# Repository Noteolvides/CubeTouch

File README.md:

## What is it?
A cube made up of 6 PCBs that when soldered together form a cube universe.
CubeTouch is designed to create a beautiful object from PCBs but giving it all the functionality of a HID device, being able to interact with the computer as if it were a keyboard or any other HID device. 

CubeTouch is made up of the **CH552** micontroller and 6 WS2812 LEDs that illuminate the planets thanks to the diffusion of the FR4 material. This device is already loaded with a firmware that when pressing one of the 5 planets will send a combination of keys to the computer. These can be modified on the 

# Documentation and more
CubeTouch has its own [webPage](https://cubetouch.noteolvid.es/) where you can find, how to [program the device](https://cubetouch.noteolvid.es/docs/firstSteps/programming/), [examples](https://cubetouch.noteolvid.es/docs/firstSteps/examples/) and much more😊!

## Examples
### Custom Firmware
Default firmware that comes preload with the package. Its main function is to use as an external keyboard with shortcuts to increase your productivity in your daily work in the computer.
Each face is mapped with a possible combination of 3 keys, and a color to show that the keys were sent.
These can be remapped via the [web interface](https://cubetouch.noteolvid.es/keyRemapping/) thanks to [web serial](https://web.dev/serial/).
### [Easy RGB](https://cubetouch.noteolvid.es/docs/firstSteps/examples/#easy-rgb)
A simple example that receives an RGB hex value and displays it. Send hex color to the Serial Monitor following this format (R,G,B): #0B4F02
### [Chasse Lights](https://cubetouch.noteolvid.es/docs/firstSteps/examples/#chasse-text)
Moving lights.
### [Easy Touch](https://cubetouch.noteolvid.es/docs/firstSteps/examples/#easy-touch)
A simple example that when a face is touch prints the face that has received input from.
### [CDC and Keyboard](https://cubetouch.noteolvid.es/docs/firstSteps/examples/#cdc-and-keyboard)
This example echoes the next character of data it receives via the serial monitor and sends as a key also the next character send.
### [Custom Bootloader](https://cubetouch.noteolvid.es/docs/firstSteps/examples/#custom-bootloader)
This example that shows how to jump to the bootloader address to make it reprogrammable. You can send the character B, or connect the pin 11 to GND.

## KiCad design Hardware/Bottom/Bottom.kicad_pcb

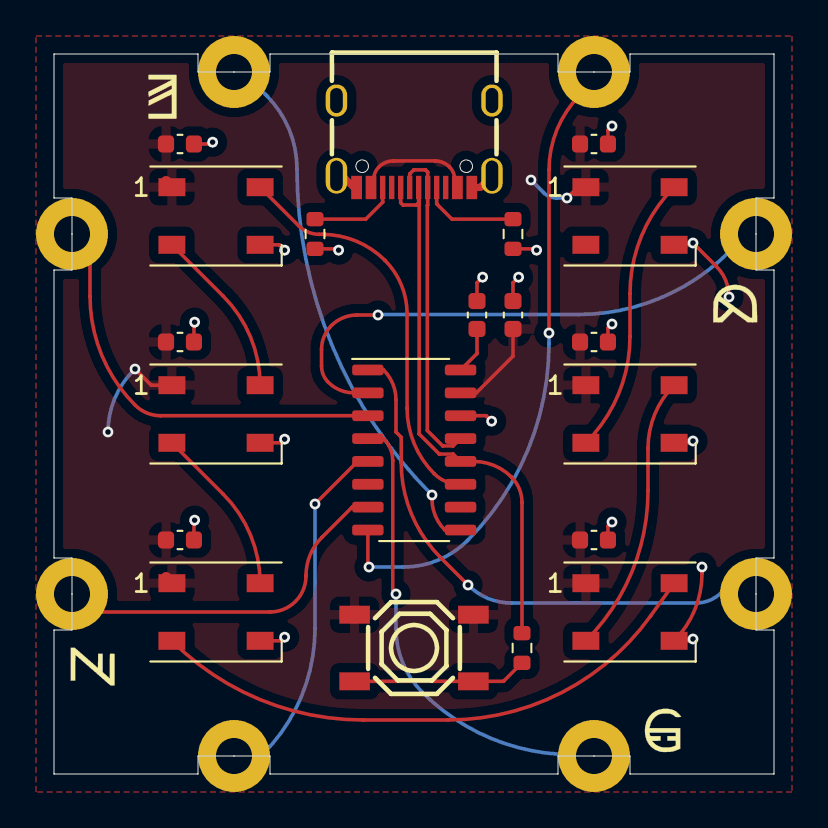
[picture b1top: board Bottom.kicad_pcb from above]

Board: 2 copper layers, 40.0 x 40.0 mm, 28 parts (0 on the bottom side), 22 nets.

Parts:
C1, C2, C3, C4, C5, C6, C7, C8: 0.1uf; C_0603_1608Metric
D1, D2, D3, D4, D5, D6: WS2812B; LED_WS2812B_PLCC4_5.0x5.0mm_P3.2mm
J1: USB_C_Receptacle_USB2.0; USB-C-SMD_KH-TYPE-C-16P
J2: Quamtum Front; Castelated
J3: Gargantua Top; Castelated
J4: Zebrum Left; Castelated
J5: Dune Right; Castelated
J6: Enkrusion Back; Castelated
J7: 3.2; Castelated
J8: 3.1; Castelated
J9: 3.0; Castelated
R1, R2: 5.1K; R_0603_1608Metric
R3: 10K; R_0603_1608Metric
SW1: Tactile Button; SW-SMD_4P-L5.1-W5.1-P3.70-LS6.5-TL-2
U1: CH552G; SO-16_3.9x9.9mm_P1.27mm

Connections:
+3V3: C2.1, U1.16 (V3.3)
DATA_LEDS: D1.4 (DIN), U1.11 (P3.4)
GND: C1.2, C2.2, C3.2, C4.2, C5.2, C6.2, C7.2, C8.2, D1.3 (VSS), D2.3 (VSS), D3.3 (VSS), D4.3 (VSS), D5.3 (VSS), D6.3 (VSS), J1.A1 (GND), J1.A12 (GND), J1.B1 (GND), J1.B12 (GND), J1.S1 (SHIELD), R1.2, R2.2, U1.14 (GND)
unnamed: D1.2 (DOUT), D2.4 (DIN)
unnamed: D2.2 (DOUT), D3.4 (DIN)
unnamed: D3.2 (DOUT), D4.4 (DIN)
unnamed: D4.2 (DOUT), D5.4 (DIN)
unnamed: D5.2 (DOUT), D6.4 (DIN)
unnamed: J1.A5 (CC1), R1.1
unnamed: J1.B5 (CC2), R2.1
unnamed: J2.1, U1.5 (P1.7)
unnamed: J3.1, U1.4 (P1.6)
unnamed: J4.1, U1.3 (P1.5)
unnamed: J5.1, U1.2 (P1.5)
unnamed: J6.1, U1.9 (P1.1)
unnamed: J7.1, U1.1 (P3.2)
unnamed: J8.1, U1.7 (P3.1)
unnamed: J9.1, U1.8 (P3.0)
unnamed: R3.2, SW1.1 (A), SW1.2 (B)
UD+: J1.A6 (D+), J1.B6 (D+), R3.1, U1.12 (P3.6)
UD-: J1.A7 (D-), J1.B7 (D-), U1.13 (P3.7)
VBUS: C1.1, C3.1, C4.1, C5.1, C6.1, C7.1, C8.1, D1.1 (VDD), D2.1 (VDD), D3.1 (VDD), D4.1 (VDD), D5.1 (VDD), D6.1 (VDD), J1.A4 (VBUS), J1.A9 (VBUS), J1.B4 (VBUS), J1.B9 (VBUS), SW1.3 (C), SW1.4 (D), U1.15 (VCC)

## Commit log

2022-01-11 init commit
2022-01-11 Init Docusaurus
2022-01-16 KeyRemapping page
2022-01-16 Added Navbar links
2022-02-06 Added docs pages
2022-02-19 Added build page
2022-02-19 Create CNAME
2022-02-19 Change baseurl
2022-02-19 Fix build
2022-02-19 Added website folder
2022-02-19 deploy: 8e7ee602b4856268e78e5021084b8bd6e064e6e0
2022-02-19 deploy: f38a8eda8bc669222fd8a9f3aa16f63e1f32a57d
2022-02-20 Added more documentation
2022-02-20 Changed github repo name
2022-02-20 deploy: 181a65fe0b3fea9ad272537e2484f867ba803c1b
2022-02-20 Deleted idea folder
2022-02-20 Deleted idea blog folder
2022-02-27 Added Examples
2022-02-27 deploy: 0cbf2b3b16d8daa06b9ea906c19a8e8f4b78ee8c
2022-02-27 Added Show code
2022-02-27 Bump prismjs from 1.26.0 to 1.27.0 in /website
    Bumps [prismjs](https://github.com/PrismJS/prism) from 1.26.0 to 1.27.0.
    - [Release notes](https://github.com/PrismJS/prism/releases)
    - [Changelog](https://github.com/PrismJS/prism/blob/master/CHANGELOG.md)
    - [Commits](https://github.com/PrismJS/prism/compare/v1.26.0...v1.27.0)
    ---
    updated-dependencies:
2022-02-27 Fix Static generation
2022-02-27 Fix package.json
2022-02-27 Fix showCode import
2022-02-27 Bump follow-redirects from 1.14.7 to 1.14.9 in /website
    Bumps [follow-redirects](https://github.com/follow-redirects/follow-redirects) from 1.14.7 to 1.14.9.
    - [Release notes](https://github.com/follow-redirects/follow-redirects/releases)
    - [Commits](https://github.com/follow-redirects/follow-redirects/compare/v1.14.7...v1.14.9)
    ---
    updated-dependencies:
    - dependency-name: follow-redirects
2022-02-27 deploy: 97d13e8eeaa0110250261fdd0a1ad4a5405fcc8b
2022-02-27 Added Hardware Files
2022-02-27 deploy: 0dc2c297448f95eb1c03892e57ea7de348dfa256
2022-02-27 Minor fix of pdf
2022-02-27 Fix default color mode
2022-02-27 deploy: bc7697fcfbed3c16eb4bd11b6adb82788a24c445
2022-05-06 Fix some web serial problems
2022-05-08 Add front page
2022-05-08 Added Manual
2022-05-08 deploy: 011e3b73cc76ed24a7d7dd245d3f108ad78cf3da
2022-05-08 Change Base Url
2022-05-08 deploy: c829220ddc20aa784e0e6fdc42c2031352960e47
2022-05-08 Change links
2022-05-08 deploy: e4e3f1735be51a8b8a455711eda8928a08772ce4
2022-05-14 Update for phones
2022-05-14 deploy: 1d209d0ba55bf83175572935e9dc82cd9e0ef1ae
2022-05-15 Update for gitHub Pages
2022-05-15 deploy: 7f5da544b2cff58458004491ebf75c12dc09a40e
2022-05-15 deploy: 4cfc364148f2cc074fd1b920169d2018045ba5d9
2022-06-06 Added theme-github-codeblock
2022-06-06 deploy: 155b1a9e1d7e78debd0fb0561092ae9310cd4f30
2022-06-06 Change embeded code to link to git
2022-06-06 Bump async from 2.6.3 to 2.6.4 in /website
    Bumps [async](https://github.com/caolan/async) from 2.6.3 to 2.6.4.
    - [Release notes](https://github.com/caolan/async/releases)
    - [Changelog](https://github.com/caolan/async/blob/v2.6.4/CHANGELOG.md)
    - [Commits](https://github.com/caolan/async/compare/v2.6.3...v2.6.4)
    ---
    updated-dependencies:
2022-06-06 deploy: 24f02c1b062c42d8d2200e64108483be5045f236
2022-06-06 Bump minimist from 1.2.5 to 1.2.6 in /website
    Bumps [minimist](https://github.com/substack/minimist) from 1.2.5 to 1.2.6.
    - [Release notes](https://github.com/substack/minimist/releases)
    - [Commits](https://github.com/substack/minimist/compare/1.2.5...1.2.6)
    ---
    updated-dependencies:
    - dependency-name: minimist
2022-06-06 deploy: 3555fe1dcdb755c83f685fc5b68485518ad3a9ae
2022-09-24 Fix error in disconnect
2022-09-24 deploy: 82a8c7c53ad3536182cb7bd6144b4fc65b628a10
2023-12-14 working new arduino core
2023-12-14 feat: Add save success notification in key remapping
    In the key remapping module, a save success notification has been included. This notification will be shown to the user once their configuration is successfully saved. The changes also enhance the me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
2023-12-14 refactor: name of usb CDC+HID
2023-12-14 deploy: cc9674aebbcfc0532bc00840c2e91fad81d9d60c
2023-12-15 refactor: improve code as new version of ch55duino
2023-12-15 refactor: improve touch code
2023-12-15 refactor: remove prints
2023-12-15 refactor: leds
2023-12-15 feat: improve touch and reafactor name of usb
2023-12-15 fix: letter t in keycode and add delay
2023-12-19 fix: reading of memory
2023-12-19 Revert "fix: reading of memory"
    This reverts commit d0b14fa5e5f659f264dcf041e80c56d27373668f.
2023-12-19 feat: cname
2023-12-19 deploy: aecbafdbe335112f2e5fa5a500dab9cc3193e87a
2023-12-19 refactor: update links
2023-12-19 deploy: c545da597390ec5f7d83583f2fdd96e2fe360b97
2023-12-20 Bump @babel/traverse from 7.17.3 to 7.23.6 in /website
    Bumps [@babel/traverse](https://github.com/babel/babel/tree/HEAD/packages/babel-traverse) from 7.17.3 to 7.23.6.
    - [Release notes](https://github.com/babel/babel/releases)
    - [Changelog](https://github.com/babel/babel/blob/main/CHANGELOG.md)
    - [Commits](https://github.com/babel/babel/commits/v7.23.6/packages/babel-traverse)
    ---
    updated-dependencies:
2023-12-25 feat: change manual page and fix upload of firmware and upload script
2023-12-25 fix: added release in mapping
2023-12-25 deploy: 9c8f64ce18a63d143e03a2d4385b8e2af4a5f783
